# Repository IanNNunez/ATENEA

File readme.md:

Athena is a TKL keyboard inspired by https://github.com/coseyfannitutti/ mysterium. It uses some of cftkb's kicad libraries
as well as its USBaspLoader build. 

Known issues:
	- Diode 84 is not directly connected to the MCU, it will be fixed for the next revision.
	- Some traces near the FN key could not be completed in the manufacturing process, more clearence is needed.
	- The silkscreen for the BOOT and RESET buttons are not visible, new and clearer silkscreens will be added.
	- The MOSI and MISO pins on the MCU are swapped, does not affect the behaviour of the keyboard it needs to be taken into account when uploading the firmware. It will be fixed for the next revision.
	- The 2u backspace key is not in the correct position, it will be fixed for the next revision.

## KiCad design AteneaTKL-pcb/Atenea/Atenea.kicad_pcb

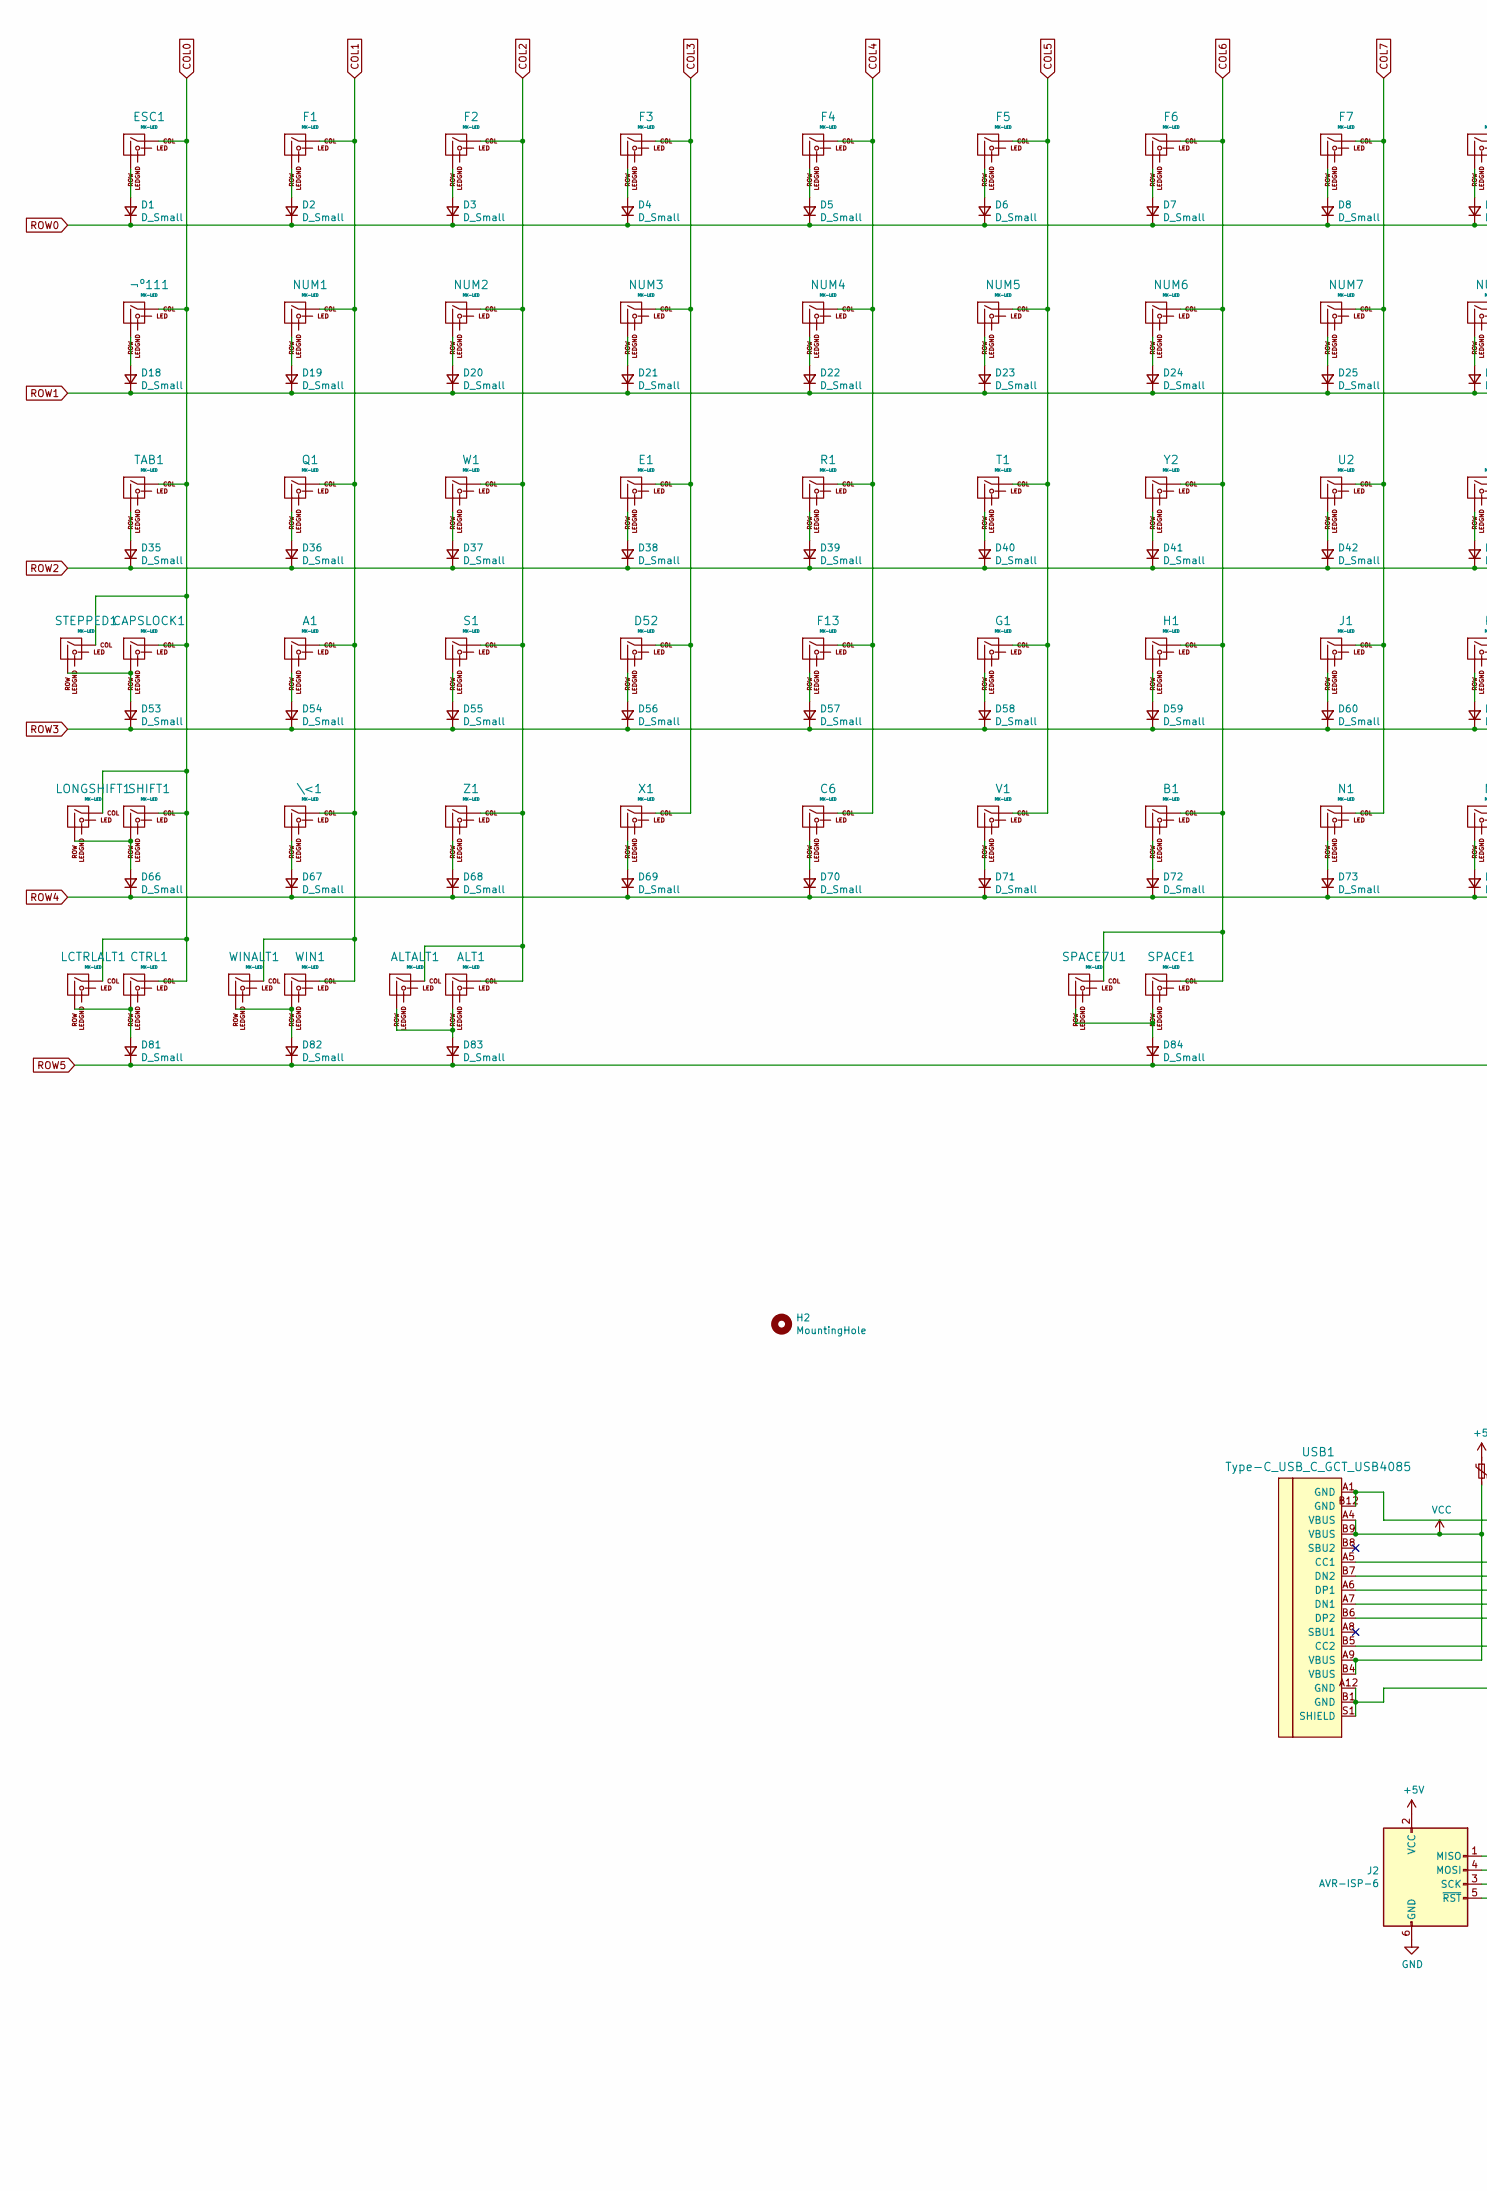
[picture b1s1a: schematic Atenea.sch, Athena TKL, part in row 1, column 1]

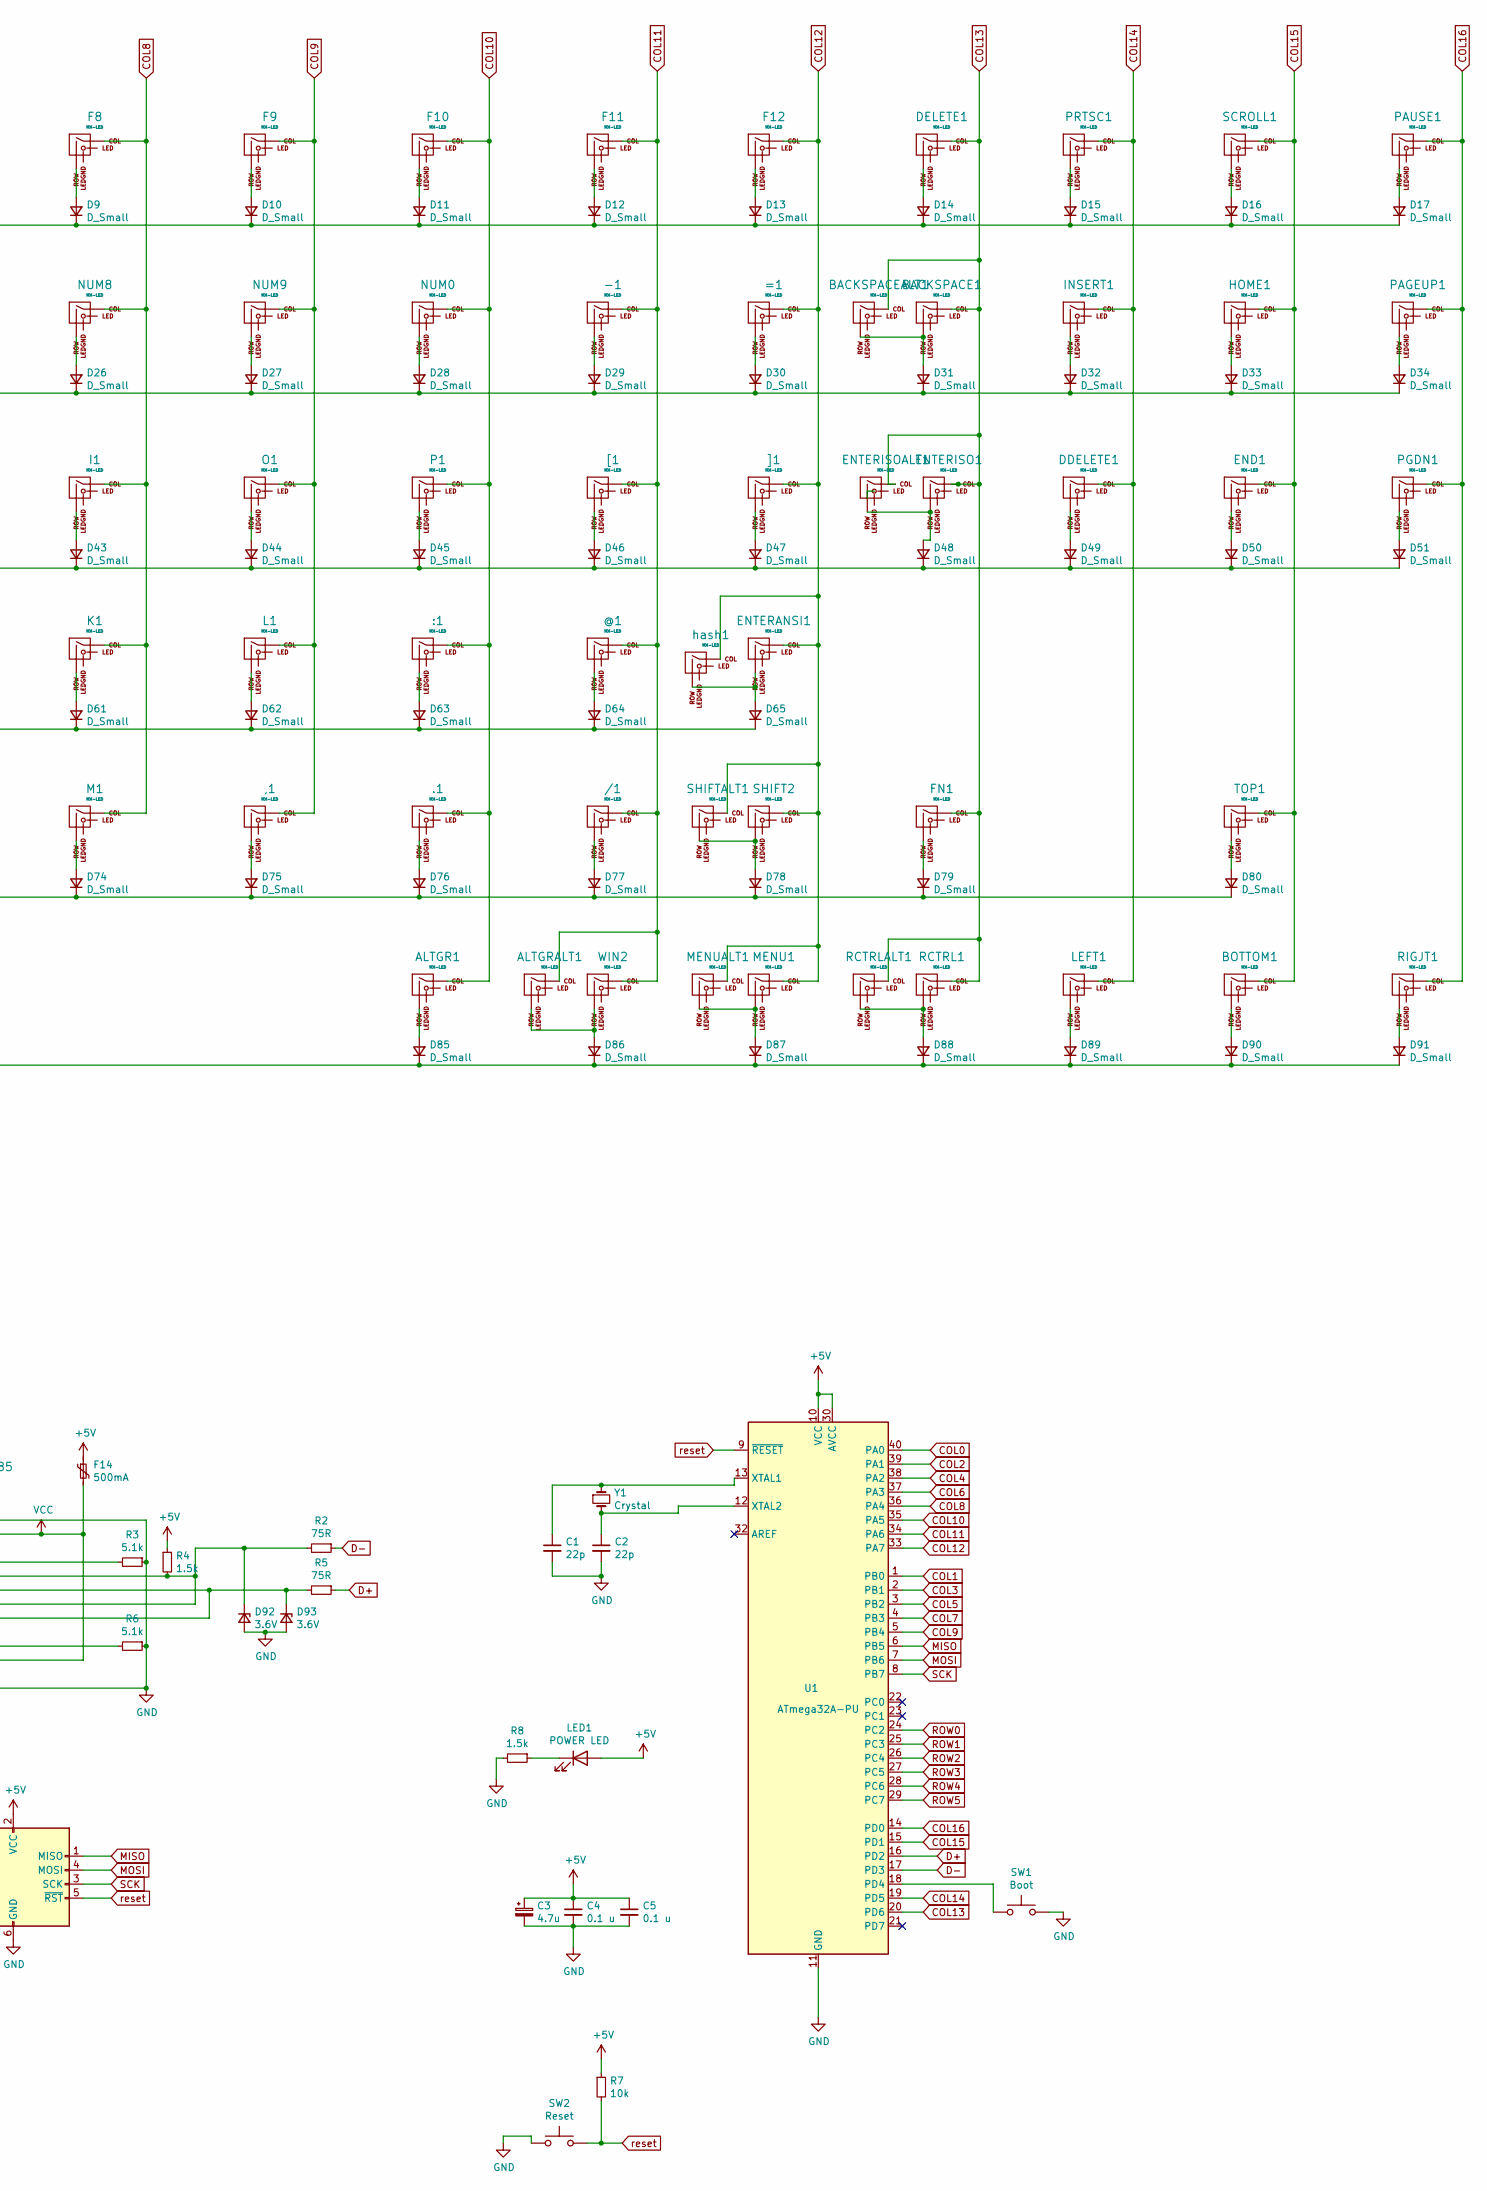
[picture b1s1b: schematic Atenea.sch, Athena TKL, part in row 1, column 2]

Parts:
,1: MX-LED; SW_Cherry_MX_1.00u_PCB
-1: MX-LED; SW_Cherry_MX_1.00u_PCB
.1: MX-LED; SW_Cherry_MX_1.00u_PCB
/1: MX-LED; SW_Cherry_MX_1.00u_PCB
:1: MX-LED; SW_Cherry_MX_1.00u_PCB
=1: MX-LED; SW_Cherry_MX_1.00u_PCB
@1: MX-LED; SW_Cherry_MX_1.00u_PCB
A1: MX-LED; SW_Cherry_MX_1.00u_PCB
ALT1: MX-LED; SW_Cherry_MX_1.00u_PCB
ALTALT1: MX-LED; SW_Cherry_MX_1.00u_PCB
ALTGR1: MX-LED; SW_Cherry_MX_1.00u_PCB
ALTGRALT1: MX-LED; SW_Cherry_MX_1.00u_PCB
B1: MX-LED; SW_Cherry_MX_1.00u_PCB
BACKSPACE1: MX-LED; MX-2U
BACKSPACEALT1: MX-LED; SW_Cherry_MX_1.00u_PCB
BOTTOM1: MX-LED; SW_Cherry_MX_1.00u_PCB
C1, C2: 22p; C_Disc_D3.0mm_W1.6mm_P2.50mm
C3: 4.7u; CP_Radial_D4.0mm_P1.50mm
C4, C5: 0.1 u; C_Disc_D4.3mm_W1.9mm_P5.00mm
C6: MX-LED; SW_Cherry_MX_1.00u_PCB
CAPSLOCK1: MX-LED; SW_Cherry_MX_1.00u_PCB
CTRL1: MX-LED; SW_Cherry_MX_1.00u_PCB
D1, D2, D3, D4, D5, D6, D7, D8, D9, D10, D11, D12, D13, D14, D15, D16, D17, D18, D19, D20, D21, D22, D23, D24, D25, D26, D27, D28, D29, D30, D31, D32, D33, D34, D35, D36, D37, D38, D39, D40, D41, D42, D43, D44, D45, D46, D47, D48, D49, D50, D51, D53, D54, D55, D56, D57, D58, D59, D60, D61, D62, D63, D64, D65, D66, D67, D68, D69, D70, D71, D72, D73, D74, D75, D76, D77, D78, D79, D80, D81, D82, D83, D84, D85, D86, D87, D88, D89, D90, D91: D_Small; D_DO-35_SOD27_P5.08mm_Horizontal
D52: MX-LED; SW_Cherry_MX_1.00u_PCB
D92, D93: 3.6V; D_DO-35_SOD27_P5.08mm_Horizontal
DDELETE1: MX-LED; SW_Cherry_MX_1.00u_PCB
DELETE1: MX-LED; SW_Cherry_MX_1.00u_PCB
E1: MX-LED; SW_Cherry_MX_1.00u_PCB
END1: MX-LED; SW_Cherry_MX_1.00u_PCB
ENTERANSI1: MX-LED; MX-2.25U
ENTERISO1: MX-LED; MX-ISO-ReversedStabilizers
ENTERISOALT1: MX-LED; SW_Cherry_MX_1.00u_PCB
ESC1: MX-LED; SW_Cherry_MX_1.00u_PCB
F1, F2, F3, F4, F5, F6, F7, F8, F9, F10, F11, F12, F13: MX-LED; SW_Cherry_MX_1.00u_PCB
F14: 500mA; polyfuse_5.1mm
FN1: MX-LED; SW_Cherry_MX_1.00u_PCB
G1: MX-LED; SW_Cherry_MX_1.00u_PCB
H1: MX-LED; SW_Cherry_MX_1.00u_PCB
H2: MountingHole; MountingHole_2.2mm_M2
HOME1: MX-LED; SW_Cherry_MX_1.00u_PCB
I1: MX-LED; SW_Cherry_MX_1.00u_PCB
INSERT1: MX-LED; SW_Cherry_MX_1.00u_PCB
J1: MX-LED; SW_Cherry_MX_1.00u_PCB
J2: AVR-ISP-6; AVR_ICSP_3x2
K1: MX-LED; SW_Cherry_MX_1.00u_PCB
L1: MX-LED; SW_Cherry_MX_1.00u_PCB
LCTRLALT1: MX-LED; SW_Cherry_MX_1.00u_PCB
LED1: POWER LED; LED_D3.0mm
LEFT1: MX-LED; SW_Cherry_MX_1.00u_PCB
LONGSHIFT1: MX-LED; MX-2.25U
M1: MX-LED; SW_Cherry_MX_1.00u_PCB
MENU1: MX-LED; SW_Cherry_MX_1.00u_PCB
MENUALT1: MX-LED; SW_Cherry_MX_1.00u_PCB
N1: MX-LED; SW_Cherry_MX_1.00u_PCB
NUM0, NUM1, NUM2, NUM3, NUM4, NUM5, NUM6, NUM7, NUM8, NUM9: MX-LED; SW_Cherry_MX_1.00u_PCB
O1: MX-LED; SW_Cherry_MX_1.00u_PCB
P1: MX-LED; SW_Cherry_MX_1.00u_PCB
PAGEUP1: MX-LED; SW_Cherry_MX_1.00u_PCB
PAUSE1: MX-LED; SW_Cherry_MX_1.00u_PCB
PGDN1: MX-LED; SW_Cherry_MX_1.00u_PCB
PRTSC1: MX-LED; SW_Cherry_MX_1.00u_PCB
Q1: MX-LED; SW_Cherry_MX_1.00u_PCB
R1: MX-LED; SW_Cherry_MX_1.00u_PCB
R2, R5: 75R; R_Axial_DIN0204_L3.6mm_D1.6mm_P7.62mm_Horizontal
R3, R6: 5.1k; R_Axial_DIN0204_L3.6mm_D1.6mm_P7.62mm_Horizontal
R4, R8: 1.5k; R_Axial_DIN0204_L3.6mm_D1.6mm_P7.62mm_Horizontal
R7: 10k; R_Axial_DIN0204_L3.6mm_D1.6mm_P7.62mm_Horizontal
RCTRL1: MX-LED; SW_Cherry_MX_1.00u_PCB
RCTRLALT1: MX-LED; SW_Cherry_MX_1.00u_PCB
RIGJT1: MX-LED; SW_Cherry_MX_1.00u_PCB
S1: MX-LED; SW_Cherry_MX_1.00u_PCB
SCROLL1: MX-LED; SW_Cherry_MX_1.00u_PCB
SHIFT1, SHIFT2: MX-LED; SW_Cherry_MX_1.00u_PCB
SHIFTALT1: MX-LED; MX-2.75U
SPACE1, SPACE7U1: MX-LED; SW_Cherry_MX_1.00u_PCB
STEPPED1: MX-LED; SW_Cherry_MX_1.00u_PCB
SW1: Boot; SW_PUSH_6mm
SW2: Reset; SW_PUSH_6mm
T1: MX-LED; SW_Cherry_MX_1.00u_PCB
TAB1: MX-LED; SW_Cherry_MX_1.00u_PCB
TOP1: MX-LED; SW_Cherry_MX_1.00u_PCB
U1: ATmega32A-PU; DIP-40_W15.24mm
U2: MX-LED; SW_Cherry_MX_1.00u_PCB
USB1: Type-C_USB_C_GCT_USB4085; USB_C_GCT_USB4085
V1: MX-LED; SW_Cherry_MX_1.00u_PCB
W1: MX-LED; SW_Cherry_MX_1.00u_PCB
WIN1, WIN2: MX-LED; SW_Cherry_MX_1.00u_PCB
WINALT1: MX-LED; SW_Cherry_MX_1.00u_PCB
X1: MX-LED; SW_Cherry_MX_1.00u_PCB
Y1: Crystal; Crystal_HC49-4H_Vertical
Y2: MX-LED; SW_Cherry_MX_1.00u_PCB
Z1: MX-LED; SW_Cherry_MX_1.00u_PCB
[1: MX-LED; SW_Cherry_MX_1.00u_PCB
\<1: MX-LED; SW_Cherry_MX_1.00u_PCB
]1: MX-LED; SW_Cherry_MX_1.00u_PCB
hash1: MX-LED; SW_Cherry_MX_1.00u_PCB
¬º111: MX-LED; SW_Cherry_MX_1.00u_PCB

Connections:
+5V: C3.1, C4.1, C5.1, F14.1, J2.2 (VCC), LED1.2 (A), R4.1, R7.1, U1.10 (VCC), U1.30 (AVCC)
COL0: CAPSLOCK1.1 (COL), CTRL1.1 (COL), ESC1.1 (COL), LCTRLALT1.1 (COL), LONGSHIFT1.1 (COL), SHIFT1.1 (COL), STEPPED1.1 (COL), TAB1.1 (COL), U1.40 (PA0), ¬º111.1 (COL); also elsewhere on the board
COL1: A1.1 (COL), F1.1 (COL), NUM1.1 (COL), Q1.1 (COL), U1.1 (PB0), WIN1.1 (COL), WINALT1.1 (COL), \<1.1 (COL)
COL2: ALT1.1 (COL), ALTALT1.1 (COL), F2.1 (COL), NUM2.1 (COL), S1.1 (COL), U1.39 (PA1), W1.1 (COL), Z1.1 (COL)
COL3: D52.1 (COL), E1.1 (COL), F3.1 (COL), NUM3.1 (COL), U1.2 (PB1), X1.1 (COL)
COL4: C6.1 (COL), F4.1 (COL), F13.1 (COL), NUM4.1 (COL), R1.1 (COL), U1.38 (PA2)
COL5: F5.1 (COL), G1.1 (COL), NUM5.1 (COL), T1.1 (COL), U1.3 (PB2), V1.1 (COL)
COL6: B1.1 (COL), F6.1 (COL), H1.1 (COL), NUM6.1 (COL), SPACE1.1 (COL), SPACE7U1.1 (COL), U1.37 (PA3), Y2.1 (COL)
COL7: F7.1 (COL), J1.1 (COL), N1.1 (COL), NUM7.1 (COL), U1.4 (PB3), U2.1 (COL)
COL8: F8.1 (COL), I1.1 (COL), K1.1 (COL), M1.1 (COL), NUM8.1 (COL), U1.36 (PA4)
COL9: ,1.1 (COL), F9.1 (COL), L1.1 (COL), NUM9.1 (COL), O1.1 (COL), U1.5 (PB4)
COL10: .1.1 (COL), :1.1 (COL), ALTGR1.1 (COL), F10.1 (COL), NUM0.1 (COL), P1.1 (COL), U1.35 (PA5)
COL11: -1.1 (COL), /1.1 (COL), @1.1 (COL), ALTGRALT1.1 (COL), F11.1 (COL), U1.34 (PA6), WIN2.1 (COL), [1.1 (COL)
COL12: =1.1 (COL), ENTERANSI1.1 (COL), F12.1 (COL), MENU1.1 (COL), MENUALT1.1 (COL), SHIFT2.1 (COL), SHIFTALT1.1 (COL), U1.33 (PA7), ]1.1 (COL), hash1.1 (COL)
COL13: BACKSPACE1.1 (COL), BACKSPACEALT1.1 (COL), DELETE1.1 (COL), ENTERISO1.1 (COL), ENTERISOALT1.1 (COL), FN1.1 (COL), RCTRL1.1 (COL), RCTRLALT1.1 (COL), U1.20 (PD6)
COL14: DDELETE1.1 (COL), INSERT1.1 (COL), LEFT1.1 (COL), PRTSC1.1 (COL), U1.19 (PD5)
COL15: BOTTOM1.1 (COL), END1.1 (COL), HOME1.1 (COL), SCROLL1.1 (COL), TOP1.1 (COL), U1.15 (PD1)
COL16: PAGEUP1.1 (COL), PAUSE1.1 (COL), PGDN1.1 (COL), RIGJT1.1 (COL), U1.14 (PD0)
D+: R5.1, U1.16 (PD2)
D-: R2.1, U1.17 (PD3)
GND: C1.2, C2.2, C3.2, C4.2, C5.2, D92.2 (A), D93.2 (A), J2.6 (GND), R3.1, R6.1, R8.2, SW1.2, SW2.1, U1.11 (GND), U1.31 (GND), USB1.A1 (GND), USB1.A12 (GND), USB1.B1 (GND), USB1.B12 (GND), USB1.S1 (SHIELD)
MISO: J2.1 (MISO), U1.6 (PB5)
MOSI: J2.4 (MOSI), U1.7 (PB6)
unnamed: ,1.2 (ROW), D75.2 (A)
unnamed: -1.2 (ROW), D29.2 (A)
unnamed: .1.2 (ROW), D76.2 (A)
unnamed: /1.2 (ROW), D77.2 (A)
unnamed: :1.2 (ROW), D63.2 (A)
unnamed: =1.2 (ROW), D30.2 (A)
unnamed: @1.2 (ROW), D64.2 (A)
unnamed: A1.2 (ROW), D54.2 (A)
unnamed: ALT1.2 (ROW), ALTALT1.2 (ROW), D83.2 (A)
unnamed: ALTGR1.2 (ROW), D85.2 (A)
unnamed: ALTGRALT1.2 (ROW), D86.2 (A), WIN2.2 (ROW)
unnamed: B1.2 (ROW), D72.2 (A)
unnamed: BACKSPACE1.2 (ROW), BACKSPACEALT1.2 (ROW), D31.2 (A)
unnamed: BOTTOM1.2 (ROW), D90.2 (A)
unnamed: C1.1, U1.13 (XTAL1), Y1.1
unnamed: C2.1, U1.12 (XTAL2), Y1.2
unnamed: C6.2 (ROW), D70.2 (A)
unnamed: CAPSLOCK1.2 (ROW), D53.2 (A), STEPPED1.2 (ROW)
unnamed: CTRL1.2 (ROW), D81.2 (A), LCTRLALT1.2 (ROW)
unnamed: D1.2 (A), ESC1.2 (ROW)
unnamed: D2.2 (A), F1.2 (ROW)
unnamed: D3.2 (A), F2.2 (ROW)
unnamed: D4.2 (A), F3.2 (ROW)
unnamed: D5.2 (A), F4.2 (ROW)
unnamed: D6.2 (A), F5.2 (ROW)
unnamed: D7.2 (A), F6.2 (ROW)
unnamed: D8.2 (A), F7.2 (ROW)
unnamed: D9.2 (A), F8.2 (ROW)
unnamed: D10.2 (A), F9.2 (ROW)
unnamed: D11.2 (A), F10.2 (ROW)
unnamed: D12.2 (A), F11.2 (ROW)
unnamed: D13.2 (A), F12.2 (ROW)
unnamed: D14.2 (A), DELETE1.2 (ROW)
unnamed: D15.2 (A), PRTSC1.2 (ROW)
unnamed: D16.2 (A), SCROLL1.2 (ROW)
unnamed: D17.2 (A), PAUSE1.2 (ROW)
unnamed 61: D18.2 (A), ¬º111.2 (ROW); also elsewhere on the board
unnamed: D19.2 (A), NUM1.2 (ROW)
unnamed: D20.2 (A), NUM2.2 (ROW)
unnamed: D21.2 (A), NUM3.2 (ROW)
unnamed: D22.2 (A), NUM4.2 (ROW)
unnamed: D23.2 (A), NUM5.2 (ROW)
unnamed: D24.2 (A), NUM6.2 (ROW)
unnamed: D25.2 (A), NUM7.2 (ROW)
unnamed: D26.2 (A), NUM8.2 (ROW)
unnamed: D27.2 (A), NUM9.2 (ROW)
unnamed: D28.2 (A), NUM0.2 (ROW)
unnamed: D32.2 (A), INSERT1.2 (ROW)
unnamed: D33.2 (A), HOME1.2 (ROW)
unnamed: D34.2 (A), PAGEUP1.2 (ROW)
unnamed: D35.2 (A), TAB1.2 (ROW)
unnamed: D36.2 (A), Q1.2 (ROW)
unnamed: D37.2 (A), W1.2 (ROW)
unnamed: D38.2 (A), E1.2 (ROW)
unnamed: D39.2 (A), R1.2 (ROW)
unnamed: D40.2 (A), T1.2 (ROW)
unnamed: D41.2 (A), Y2.2 (ROW)
unnamed: D42.2 (A), U2.2 (ROW)
unnamed: D43.2 (A), I1.2 (ROW)
unnamed: D44.2 (A), O1.2 (ROW)
unnamed: D45.2 (A), P1.2 (ROW)
unnamed: D46.2 (A), [1.2 (ROW)
unnamed: D47.2 (A), ]1.2 (ROW)
unnamed: D48.2 (A), ENTERISO1.2 (ROW), ENTERISOALT1.2 (ROW)
unnamed: D49.2 (A), DDELETE1.2 (ROW)
unnamed: D50.2 (A), END1.2 (ROW)
unnamed: D51.2 (A), PGDN1.2 (ROW)
unnamed: D52.2 (ROW), D56.2 (A)
unnamed: D55.2 (A), S1.2 (ROW)
unnamed: D57.2 (A), F13.2 (ROW)
unnamed: D58.2 (A), G1.2 (ROW)
unnamed: D59.2 (A), H1.2 (ROW)
unnamed: D60.2 (A), J1.2 (ROW)
unnamed: D61.2 (A), K1.2 (ROW)
unnamed: D62.2 (A), L1.2 (ROW)
unnamed: D65.2 (A), ENTERANSI1.2 (ROW), hash1.2 (ROW)
unnamed: D66.2 (A), LONGSHIFT1.2 (ROW), SHIFT1.2 (ROW)
unnamed: D67.2 (A), \<1.2 (ROW)
unnamed: D68.2 (A), Z1.2 (ROW)
unnamed: D69.2 (A), X1.2 (ROW)
unnamed: D71.2 (A), V1.2 (ROW)
unnamed: D73.2 (A), N1.2 (ROW)
unnamed: D74.2 (A), M1.2 (ROW)
unnamed: D78.2 (A), SHIFT2.2 (ROW), SHIFTALT1.2 (ROW)
unnamed: D79.2 (A), FN1.2 (ROW)
unnamed: D80.2 (A), TOP1.2 (ROW)
unnamed: D82.2 (A), WIN1.2 (ROW), WINALT1.2 (ROW)
unnamed: D84.2 (A), SPACE1.2 (ROW), SPACE7U1.2 (ROW)
unnamed: D87.2 (A), MENU1.2 (ROW), MENUALT1.2 (ROW)
unnamed: D88.2 (A), RCTRL1.2 (ROW), RCTRLALT1.2 (ROW)
unnamed: D89.2 (A), LEFT1.2 (ROW)
unnamed: D91.2 (A), RIGJT1.2 (ROW)
unnamed: D92.1 (K), R2.2, R4.2, USB1.A7 (DN1), USB1.B7 (DN2)
unnamed: D93.1 (K), R5.2, USB1.A6 (DP1), USB1.B6 (DP2)
unnamed: LED1.1 (K), R8.1
unnamed: R3.2, USB1.A5 (CC1)
unnamed: R6.2, USB1.B5 (CC2)
unnamed: SW1.1, U1.18 (PD4)
ROW0: D1.1 (K), D2.1 (K), D3.1 (K), D4.1 (K), D5.1 (K), D6.1 (K), D7.1 (K), D8.1 (K), D9.1 (K), D10.1 (K), D11.1 (K), D12.1 (K), D13.1 (K), D14.1 (K), D15.1 (K), D16.1 (K), D17.1 (K), U1.24 (PC2)
ROW1: D18.1 (K), D19.1 (K), D20.1 (K), D21.1 (K), D22.1 (K), D23.1 (K), D24.1 (K), D25.1 (K), D26.1 (K), D27.1 (K), D28.1 (K), D29.1 (K), D30.1 (K), D31.1 (K), D32.1 (K), D33.1 (K), D34.1 (K), U1.25 (PC3)
ROW2: D35.1 (K), D36.1 (K), D37.1 (K), D38.1 (K), D39.1 (K), D40.1 (K), D41.1 (K), D42.1 (K), D43.1 (K), D44.1 (K), D45.1 (K), D46.1 (K), D47.1 (K), D48.1 (K), D49.1 (K), D50.1 (K), D51.1 (K), U1.26 (PC4)
ROW3: D53.1 (K), D54.1 (K), D55.1 (K), D56.1 (K), D57.1 (K), D58.1 (K), D59.1 (K), D60.1 (K), D61.1 (K), D62.1 (K), D63.1 (K), D64.1 (K), D65.1 (K), U1.27 (PC5)
ROW4: D66.1 (K), D67.1 (K), D68.1 (K), D69.1 (K), D70.1 (K), D71.1 (K), D72.1 (K), D73.1 (K), D74.1 (K), D75.1 (K), D76.1 (K), D77.1 (K), D78.1 (K), D79.1 (K), D80.1 (K), U1.28 (PC6)
ROW5: D81.1 (K), D82.1 (K), D83.1 (K), D84.1 (K), D85.1 (K), D86.1 (K), D87.1 (K), D88.1 (K), D89.1 (K), D90.1 (K), D91.1 (K), U1.29 (PC7)
SCK: J2.3 (SCK), U1.8 (PB7)
VCC: F14.2, USB1.A4 (VBUS), USB1.A9 (VBUS), USB1.B4 (VBUS), USB1.B9 (VBUS)
reset: J2.5 (~RST), R7.2, SW2.2, U1.9 (~RESET)

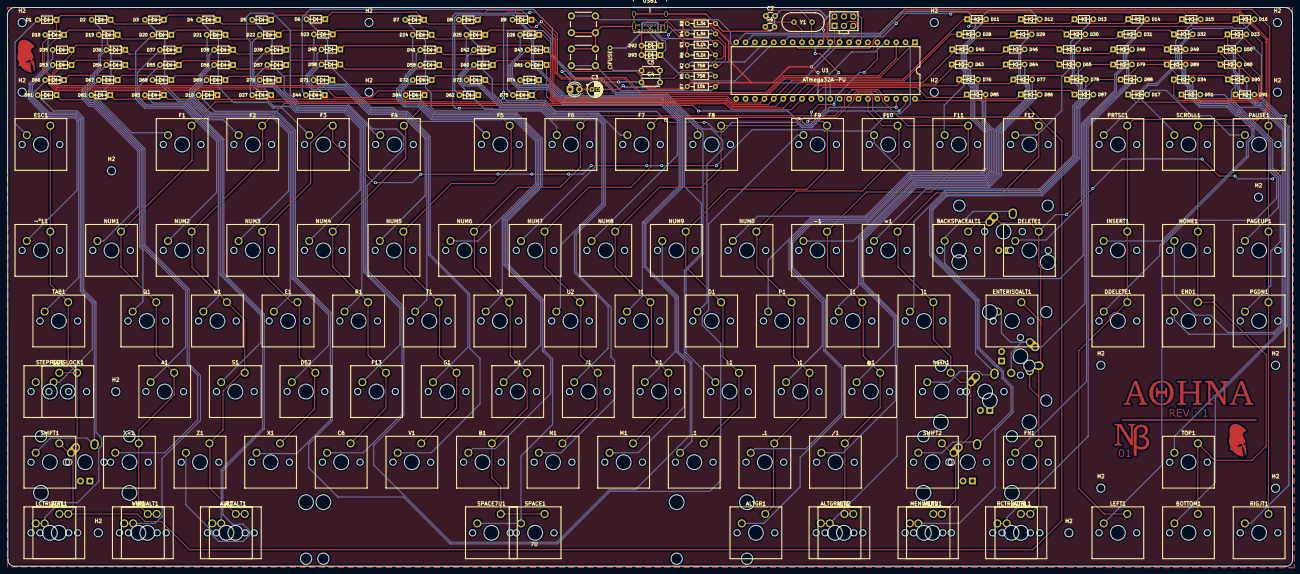
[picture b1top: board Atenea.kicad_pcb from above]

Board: 2 copper layers, 346.7 x 150.7 mm, 238 parts (0 on the bottom side), 130 nets.

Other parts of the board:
G2, G6: LOGO; athena helmet negative
G4: LOGO; athena logo
G5: LOGO; NEWblack logo
H2#2, H2#3, H2#4, H2#5, H2#6, H2#7, H2#8, H2#9, H2#10, H2#11, H2#12, H2#13, H2#14, H2#15, H2#16, H2#17: MountingHole; MountingHole_2.2mm_M2
ST62: 7U; MX-7U-Stabilizer
ST62#2: 6.25U; MX-6.25U-Stabilizer
¬º11: MX-LED; SW_Cherry_MX_1.00u_PCB

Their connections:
COL0: ¬º11.1; also elsewhere on the board
unnamed 61: ¬º11.2; also elsewhere on the board

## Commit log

2021-06-03 Proyect updated and uploaded
2021-06-03 erased unecesary stuff
2022-02-15 Added pcb files and clean up
2022-02-15 Create AteneaTKL-pcb
2022-02-15 Revert "Delete AteneaTKL-pcb"
    This reverts commit ce965d91c7369113902de39412e0e9e35ef7db22.
2022-02-15 Clean up
2022-02-15 PCB files
